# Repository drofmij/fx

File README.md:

# FX 
This repo will hold any schematic / pcb board combinations in Eagle cad format that I am working on. They may or may not work or be useful to anyone. Most of what I have been working on are in the form of boards for guitar effects.

## Projects
- [Attack of the Klones](https://github.com/drofmij/fx/tree/master/klones) (Unverified)
- [Mandarin AD200B](https://github.com/drofmij/fx/tree/master/Baja-Orange-AD200B) (Unverified)

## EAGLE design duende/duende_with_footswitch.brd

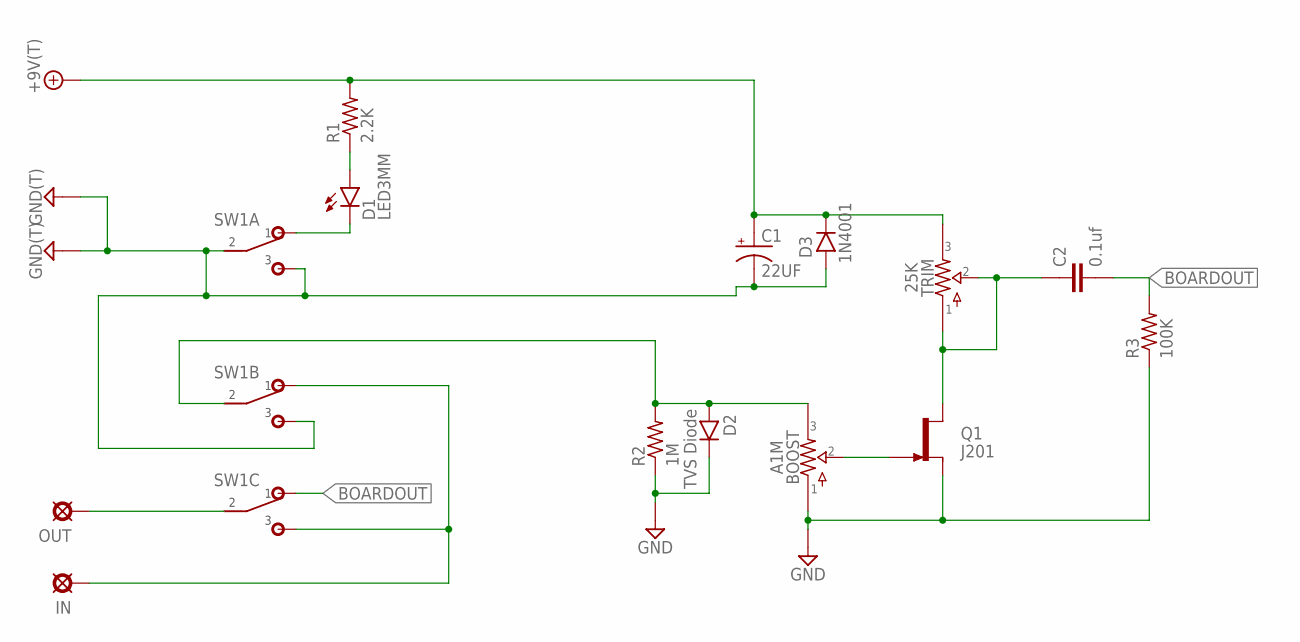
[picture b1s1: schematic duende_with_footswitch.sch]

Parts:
+9V: +9V(T); SQUARE
BOOST: A1M; PADS_SMALL
C1: 22UF; 050_020_1
C2: 0.1uf; 072X025
D1: LED3MM
D2: TVS Diode; DO41-2
D3: 1N4001; DO41-2
GND, GND1: GND(T); SQUARE
IN: PADO; ROUND
OUT: PADO; ROUND
Q1: J201; TO92-
R1: 2.2K; R0207/3
R2: 1M; R0207/3
R3: 100K; R0207/3
SW1: 3PDT
TRIM: 25K; TRIM-ALL

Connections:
+9V: +9V.1, C1.+, D3.C, R1.2, TRIM.3, TRIM.6 (3)
BOARDIN: BOOST.3, D2.A, R2.2, SW1.B2 (2)
BOARDOUT: C2.2, R3.2, SW1.C1 (1)
GND: BOOST.1, C1.-, D2.C, D3.A, GND.1, GND1.1, Q1.2 (S), R2.1, R3.1, SW1.A2 (2), SW1.A3 (3), SW1.B3 (3)
INPUT: IN.1, SW1.B1 (1), SW1.C3 (3)
unnamed: D1.K (C), SW1.A1 (1)
unnamed: D1.A, R1.1
unnamed: BOOST.2, Q1.1 (G)
unnamed: C2.1, Q1.3 (D), TRIM.1, TRIM.2, TRIM.4 (1), TRIM.5 (2)
OUTPUT: OUT.1, SW1.C2 (2)

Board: 2 copper layers, 17 parts (0 on the bottom side), 10 nets, no tracks yet.

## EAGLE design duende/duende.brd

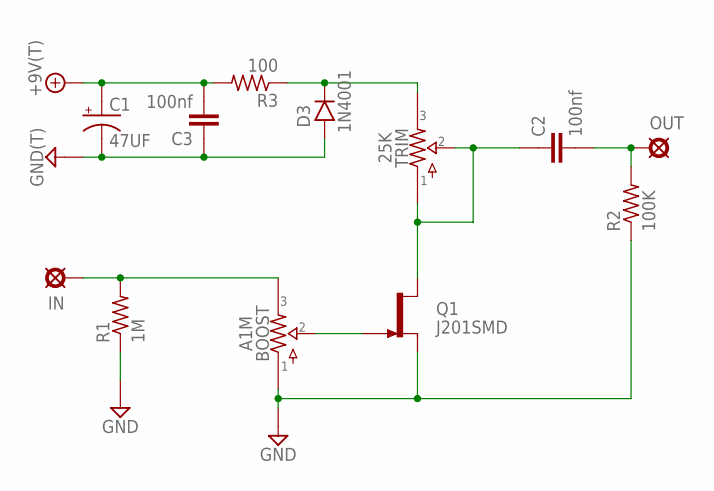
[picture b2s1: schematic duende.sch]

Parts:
+9V: +9V(T); SQUARE
BOOST: A1M; PADS_SMALL
C1: 47UF; 050_020_1
C2, C3: 100nf; 072X025
D3: 1N4001; DO41-2
GND: GND(T); SQUARE
IN: IN]; ROUND
OUT: OUT; ROUND
Q1: J201SMD; SOT23
R1: 1M; R0204/2
R2: 100K; R0204/2
R3: 100; R0204/2
TRIM: 25K; TRIM-ALL

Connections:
+9V: +9V.1, C1.+, C3.2, R3.2
FXOUT: C2.2, OUT.1, R2.2
GND: BOOST.1, C1.-, C3.1, D3.A, GND.1, Q1.E (S), R1.1, R2.1
unnamed: BOOST.3, IN.1, R1.2
unnamed: D3.C, R3.1, TRIM.3, TRIM.6 (3)
unnamed: BOOST.2, Q1.C (G)
unnamed: C2.1, Q1.B (D), TRIM.1, TRIM.2, TRIM.4 (1), TRIM.5 (2)

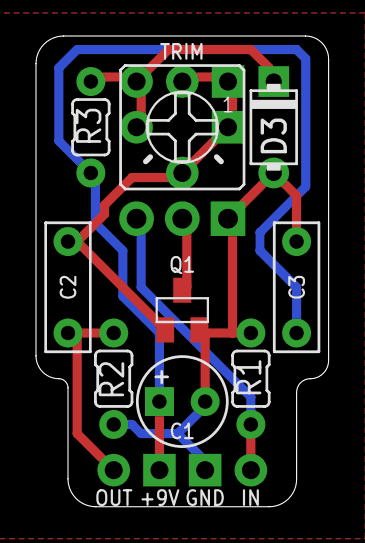
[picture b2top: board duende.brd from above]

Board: 2 copper layers, 16.3 x 26.2 mm, 14 parts (1 on the bottom side), 7 nets.

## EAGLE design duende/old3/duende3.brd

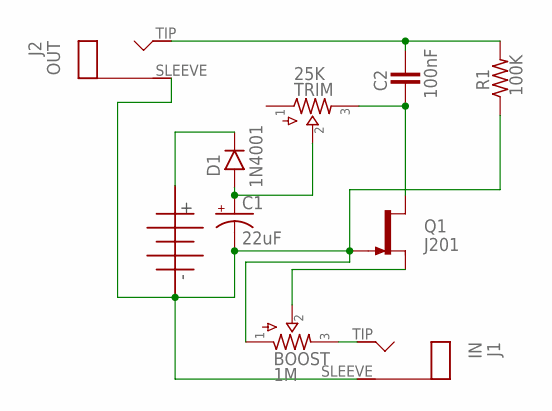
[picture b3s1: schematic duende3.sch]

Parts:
+9V: +9V; BATTERY
BOOST: 1M; PADS_LARGE
C1: 22uF; 050_020_1
C2: 100nF; BOX_SMALL
D1: 1N4001; DO41-3
J1: IN; TWO_PADS
J2: OUT; TWO_PADS
Q1: J201; TO92-
R1: 100K; R0207/3
TRIM: 25K; 2262_TRIM

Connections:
GND: +9V.P$2, BOOST.1, C1.-, J1.SLEEVE, J2.SLEEVE, Q1.1 (G), R1.1
unnamed: +9V.P$1, D1.C
unnamed: C1.+, D1.A, TRIM.2
unnamed: BOOST.2, Q1.2 (S)
unnamed: C2.2, Q1.3 (D), TRIM.3
unnamed: C2.1, J2.TIP, R1.2
unnamed: BOOST.3, J1.TIP

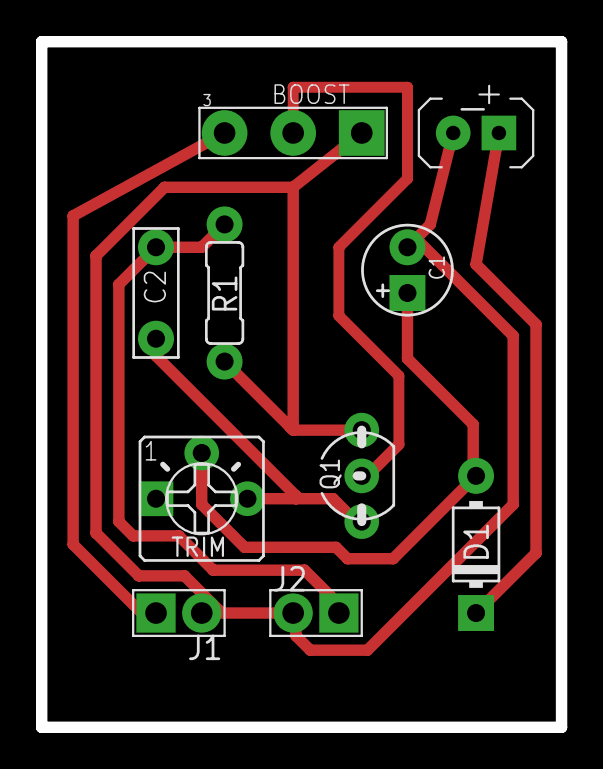
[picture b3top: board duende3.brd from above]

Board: 2 copper layers, 28.9 x 38.1 mm, 10 parts (0 on the bottom side), 7 nets.

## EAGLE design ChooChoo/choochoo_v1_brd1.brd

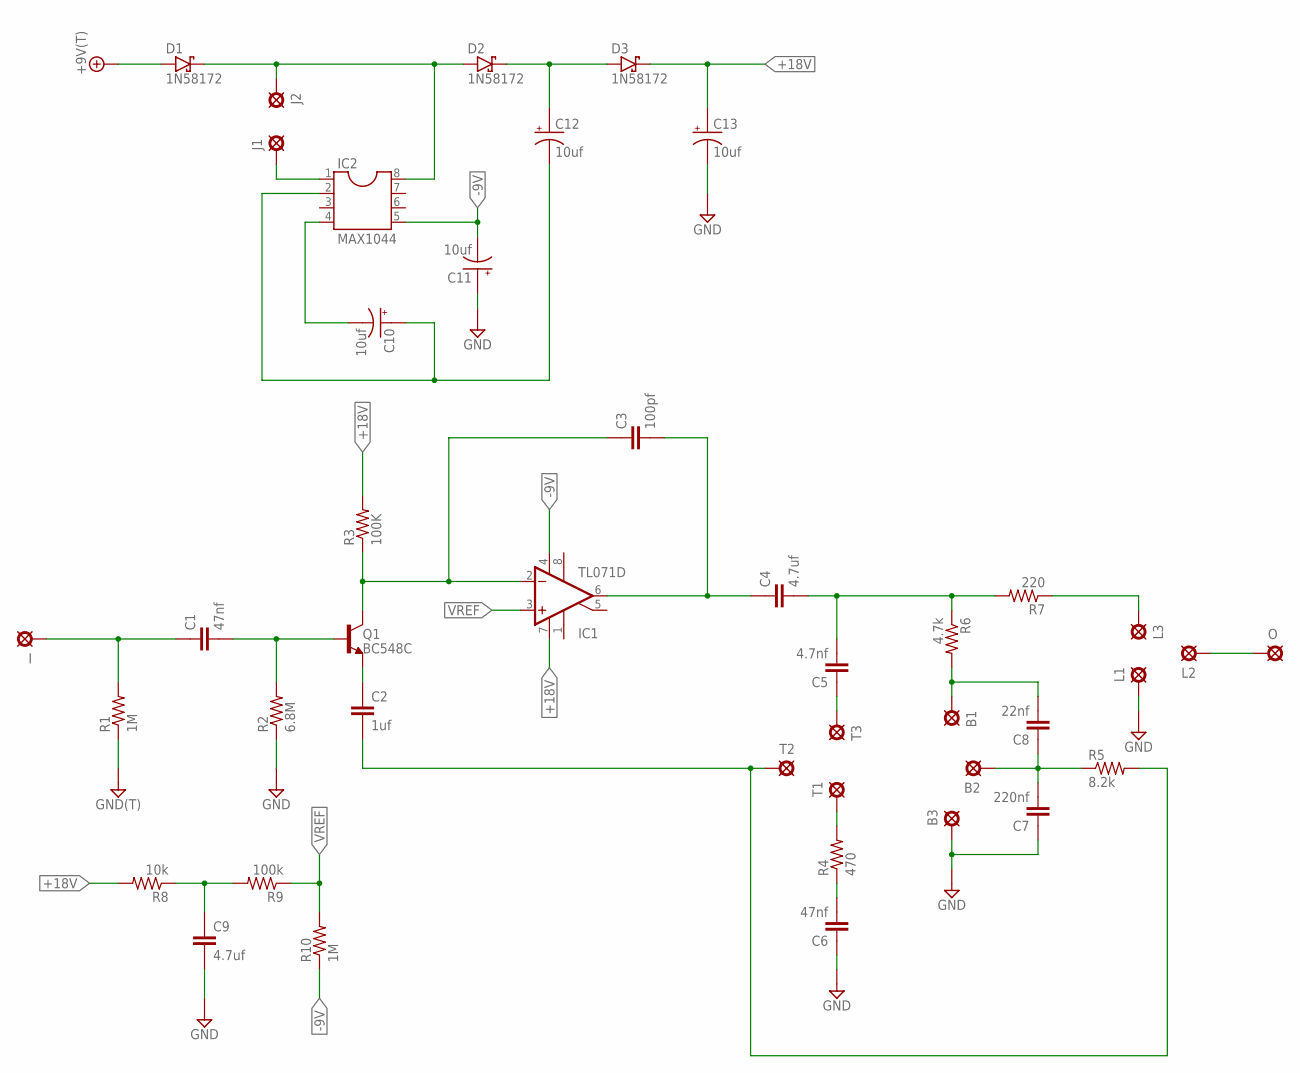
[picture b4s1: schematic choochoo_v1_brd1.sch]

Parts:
B1, B2, B3: PAD8; OCTOGON
C1, C6: 47nf; 072X025
C2: 1uf; 050X030_025
C3: 100pf; 050X030_025
C4, C9: 4.7uf; 050X030_025
C5: 4.7nf; 072X025
C7: 220nf; 072X025
C8: 22nf; 072X025
C10, C11, C12, C13: 10uf; 050_020_1
D1, D2, D3: 1N58172; DO41-2
G: GND(T); SQUARE
I: IN; ROUND
IC1: TL071D; SO08
IC2: MAX1044; DIL08
J1, J2: PAD8; OCTOGON
L1, L2, L3: PAD8; OCTOGON
O: IN; ROUND
Q1: BC548C; TO92-
R1, R10: 1M; R0204/2
R2: 6.8M; R0204/2
R3: 100K; R0204/2
R4: 470; R0204/2
R5: 8.2k; R0204/2
R6: 4.7k; R0204/2
R7: 220; R0204/2
R8: 10k; R0204/2
R9: 100k; R0204/2
T1, T2, T3: PAD8; OCTOGON
V: +9V(T); SQUARE

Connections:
+9V: D1.A, V.1
+18V: C13.+, D3.C, IC1.7 (V+), R3.2, R8.2
-9V: C11.-, IC1.4 (V-), IC2.5, R10.1
GND: B3.1, C6.1, C7.1, C9.2, C11.+, C13.-, G.1, L1.1, R1.1, R2.1
unnamed: D1.C, D2.A, IC2.8, J2.1
unnamed: C1.2, Q1.1 (B), R2.2
unnamed: C3.1, IC1.2 (-IN), Q1.2 (C), R3.1
unnamed: C2.1, Q1.3 (E)
unnamed: R4.2, T1.1
unnamed: C3.2, C4.1, IC1.6 (OUT)
unnamed: C5.1, T3.1
unnamed: C4.2, C5.2, R6.1, R7.2
unnamed: L3.1, R7.1
unnamed: C6.2, R4.1
unnamed: C12.+, D2.C, D3.A
unnamed: L2.1, O.1
unnamed: B1.1, C8.2, R6.2
unnamed: B2.1, C7.2, C8.1, R5.1
unnamed: C9.1, R8.1, R9.2
unnamed: C2.2, R5.2, T2.1
unnamed: C10.+, C12.-, IC2.2
unnamed: C10.-, IC2.4
unnamed: IC2.1, J1.1
unnamed: C1.1, I.1, R1.2
VREF: IC1.3 (+IN), R9.1, R10.2

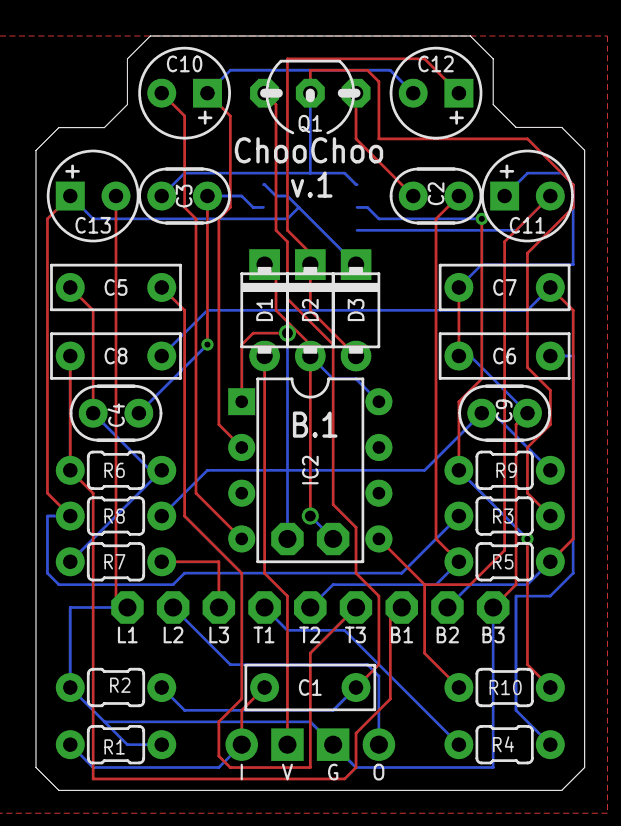
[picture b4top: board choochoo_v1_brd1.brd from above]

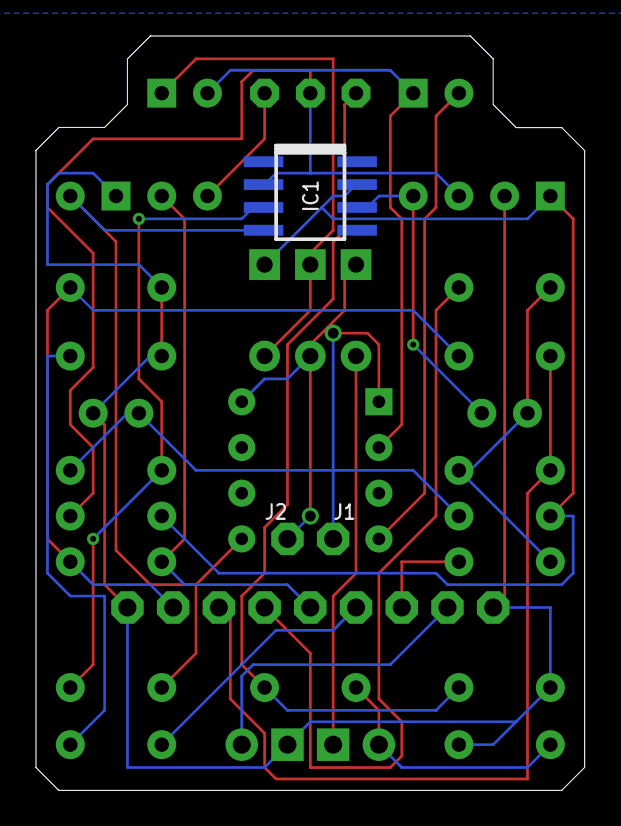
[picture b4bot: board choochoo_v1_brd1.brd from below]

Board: 2 copper layers, 30.5 x 41.9 mm, 44 parts (3 on the bottom side), 25 nets.

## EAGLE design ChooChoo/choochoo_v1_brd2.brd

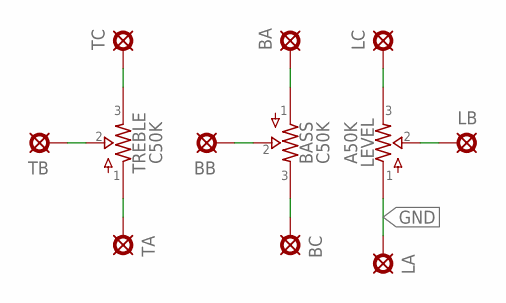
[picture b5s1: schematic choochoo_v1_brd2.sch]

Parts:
BA: PAD8; OCTOGON
BASS: C50K; 9MM_W/MOUNTS-2MMHOLES
BB: PAD8; OCTOGON
BC: PAD8; OCTOGON
LA: PAD8; OCTOGON
LB: PAD8; OCTOGON
LC: PAD8; OCTOGON
LEVEL: A50K; 9MM_W/MOUNTS-2MMHOLES
TA: PAD8; OCTOGON
TB: PAD8; OCTOGON
TC: PAD8; OCTOGON
TREBLE: C50K; 9MM_W/MOUNTS-2MMHOLES

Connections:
GND: LA.1, LEVEL.P$1 (1)
unnamed: TB.1, TREBLE.P$2 (2)
unnamed: TC.1, TREBLE.P$3 (3)
unnamed: TA.1, TREBLE.P$1 (1)
unnamed: BASS.P$3 (3), BC.1
unnamed: BASS.P$2 (2), BB.1
unnamed: BA.1, BASS.P$1 (1)
unnamed: LB.1, LEVEL.P$2 (2)
unnamed: LC.1, LEVEL.P$3 (3)

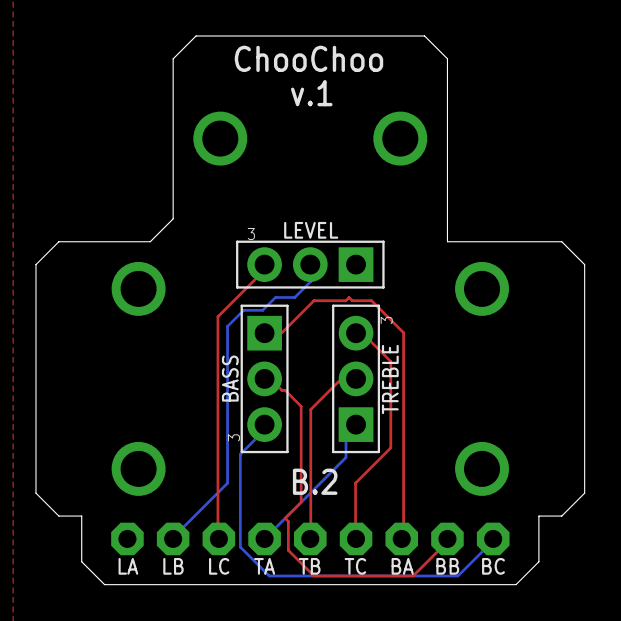
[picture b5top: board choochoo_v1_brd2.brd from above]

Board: 2 copper layers, 30.5 x 30.5 mm, 12 parts (0 on the bottom side), 9 nets.

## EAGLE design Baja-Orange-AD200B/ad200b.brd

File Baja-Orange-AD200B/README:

This is based on Baja's Clone of the Orange AD200B preamp. I built this per Johnk's version on the [original thread](http://freestompboxes.org/viewtopic.php?f=13&t=28961&view=unread&sid=48e1a8c39ae74f20a4534faedff610bc)

My understanding is that Baja built this preamp using the frequency and clipping characteristics of the original amp, as such it is not a part for part copy of the original.

Currently UNVERIFIED and planning to fit it into a 1590b once I have time to order boards and build it. If you build this before I get to it please let me know how it works out.

Transistor and opamp are SMD / SMT but should not be too bad. for the 1uf caps I was planning on using tantalum or mlcc so used a footprint that will allow it instead of the normal electrolytic ones. The board allows for top mount IN OUT jacks and top mount power jack if you want to use them.

PLEASE NOTE: I designed this to be used in conjunction with a 3pdt daughter board which has power filtering on it. As such I did not add proper power filtering to this schem / board

- [Eagle cad files](https://github.com/drofmij/fx/tree/master/Baja-Orange-AD200B)
- [Parts list CSV](https://raw.githubusercontent.com/drofmij/fx/master/Baja-Orange-AD200B/ad200b-bom.csv)

Final NOTE / Warning: This is entirely untested, I am open to input but will likely respond very asynchronously as Real Life is a bit crazy right now. There is no warranty or support included with this design.

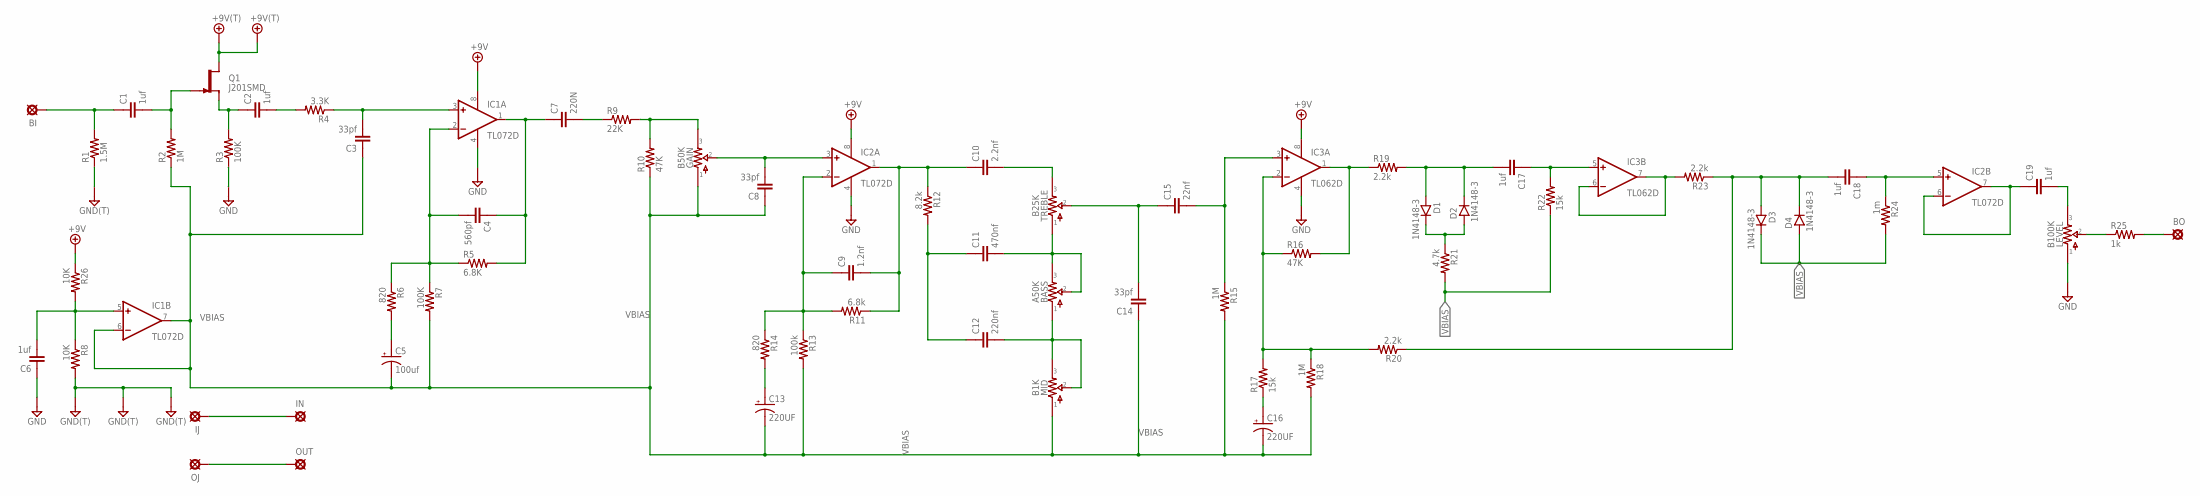
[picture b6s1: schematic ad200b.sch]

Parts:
+V: +9V(T); SQUARE
BASS: A50K; 9MM_W/MOUNTS-2MMHOLES
BI: IN; SQUARE
BO: OUT; SQUARE
C1, C2, C6, C17, C18, C19: 1uf; 050X030_025
C3, C8, C14: 33pf; 050X030_025
C4: 560pf; 050X030_025
C5: 100uf; 050_020_1
C7: 220N; 072X025
C9: 1.2nf; 072X025
C10: 2.2nf; 072X025
C11: 470nf; 072X025
C12: 220nf; 072X025
C13, C16: 220UF; 050_020_1
C15: 22nf; 072X025
D1, D2, D3, D4: 1N4148-3; DO35-3
G1, G2, G3, G4: GND(T); SQUARE
GAIN: B50K; 9MM_W/MOUNTS-2MMHOLES
IC1, IC2: TL072D; SO08
IC3: TL062D; SO08
IJ: PAD8; OCTOGON
IN: PAD8; OCTOGON
LEVEL: B100K; 9MM_W/MOUNTS-2MMHOLES
MID: B1K; 9MM_W/MOUNTS-2MMHOLES
OJ: PAD8; OCTOGON
OUT: PAD8; OCTOGON
Q1: J201SMD; SOT23
R1: 1.5M; R0204/2
R2, R15, R18: 1M; R0204/2
R3, R7: 100K; R0204/2
R4: 3.3K; R0204/2
R5: 6.8K; R0204/2
R6, R14: 820; R0204/2
R8, R26: 10K; R0204/2
R9: 22K; R0204/2
R10, R16: 47K; R0204/2
R11: 6.8k; R0204/2
R12: 8.2k; R0204/2
R13: 100k; R0204/2
R17, R22: 15k; R0204/2
R19, R20, R23: 2.2k; R0204/2
R21: 4.7k; R0204/2
R24: 1m; R0204/2
R25: 1k; R0204/2
TREBLE: B25K; 9MM_W/MOUNTS-2MMHOLES
V: +9V(T); SQUARE

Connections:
+9V: +V.1, IC1.8 (V+), IC2.8 (V+), IC3.8 (V+), Q1.B (D), R26.1, V.1
GND: C6.1, G1.1, G2.1, G3.1, G4.1, IC1.4 (V-), IC2.4 (V-), IC3.4 (V-), LEVEL.P$1 (1), R1.1, R3.1, R8.2
unnamed: BI.1, C1.1, R1.2
unnamed: C1.2, Q1.C (G), R2.2
unnamed: C2.1, Q1.E (S), R3.2
unnamed: C2.2, R4.2
unnamed: C6.2, IC1.5 (+IN), R8.1, R26.2
unnamed: C3.2, IC1.3 (+IN), R4.1
unnamed: C4.2, IC1.2 (-IN), R5.1, R6.1, R7.1
unnamed: C4.1, C7.1, IC1.1 (OUT), R5.2
unnamed: C7.2, R9.1
unnamed: GAIN.P$3 (3), R9.2, R10.2
unnamed: C5.+, R6.2
unnamed: C9.2, C10.1, IC2.1 (OUT), R11.1, R12.1
unnamed: BASS.P$1 (1), C12.2, MID.P$2 (2), MID.P$3 (3)
unnamed: C11.1, C12.1, R12.2
unnamed: C8.2, GAIN.P$2 (2), IC2.3 (+IN)
unnamed: IC3.1 (OUT), R16.2, R19.1
unnamed: C17.1, IC3.5 (+IN), R22.2
unnamed: C9.1, IC2.2 (-IN), R11.2, R13.1, R14.1
unnamed: BASS.P$2 (2), BASS.P$3 (3), C11.2, TREBLE.P$1 (1)
unnamed: C13.+, R14.2
unnamed: C17.2, D1.A, D2.C, R19.2
unnamed: C10.2, TREBLE.P$3 (3)
unnamed: D1.C, D2.A, R21.1
unnamed: C14.2, C15.1, TREBLE.P$2 (2)
unnamed: IC3.6 (-IN), IC3.7 (OUT), R23.2
unnamed: C15.2, IC3.3 (+IN), R15.1
unnamed: C18.2, D3.A, D4.C, R20.1, R23.1
unnamed: C19.1, IC2.6 (-IN), IC2.7 (OUT)
unnamed: C16.+, R17.1
unnamed: IJ.1, IN.1
unnamed: C19.2, LEVEL.P$3 (3)
unnamed: IC3.2 (-IN), R16.1, R17.2, R18.1, R20.2
unnamed: C18.1, IC2.5 (+IN), R24.1
unnamed: OJ.1, OUT.1
unnamed: LEVEL.P$2 (2), R25.1
unnamed: BO.1, R25.2
VBIAS: C3.1, C5.-, C8.1, C13.-, C14.1, C16.-, D3.C, D4.A, GAIN.P$1 (1), IC1.6 (-IN), IC1.7 (OUT), MID.P$1 (1), R2.1, R7.2, R10.1, R13.2, R15.2, R18.2, R21.2, R22.1, R24.2

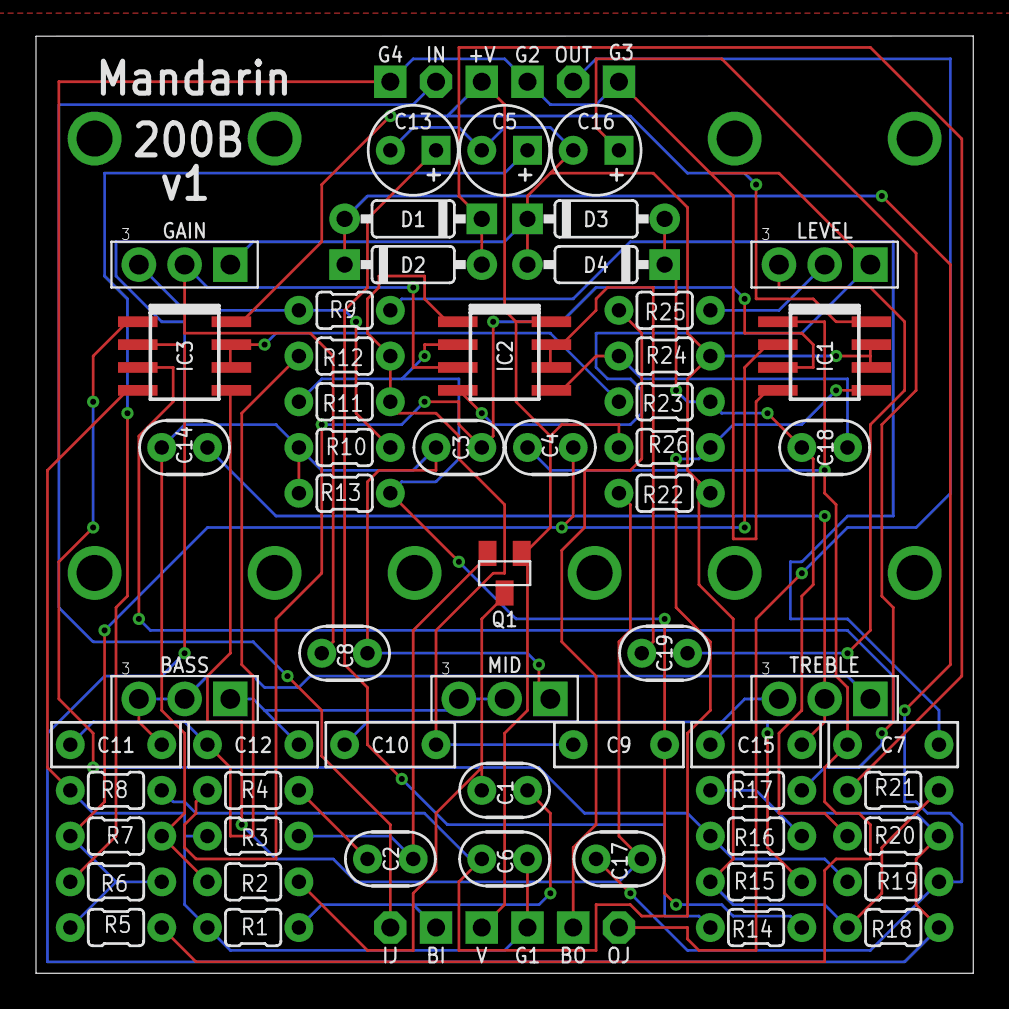
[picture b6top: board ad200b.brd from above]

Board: 2 copper layers, 52.1 x 52.1 mm, 70 parts (0 on the bottom side), 39 nets.

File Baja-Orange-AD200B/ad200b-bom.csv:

"Part";"Value";"Device";"Package";"Description";"";
"+V";"+9V(T)";"+9V(T)";"SQUARE";"+9V Voltage Supply";"";
"BASS";"A50K";"POTS9MM_MOUNTED_2MMH";"9MM_W/MOUNTS-2MMHOLES";"";"";
"BI";"IN";"PAD";"SQUARE";"PAD";"";
"BO";"OUT";"PAD";"SQUARE";"PAD";"";
"C1";"1uf";"050X030_0251";"050X030_025";"47 - 120pF";"";
"C2";"1uf";"050X030_0251";"050X030_025";"47 - 120pF";"";
"C3";"33pf";"050X030_0251";"050X030_025";"47 - 120pF";"";
"C4";"560pf";"050X030_0251";"050X030_025";"47 - 120pF";"";
"C5";"100uf";"0501";"050_020_1";"0.22 - 100uF";"";
"C6";"1uf";"050X030_0251";"050X030_025";"47 - 120pF";"";
"C7";"220N";"072X0252";"072X025";"1000pF - 0.47uF";"";
"C8";"33pf";"050X030_0251";"050X030_025";"47 - 120pF";"";
"C9";"1.2nf";"072X0252";"072X025";"1000pF - 0.47uF";"";
"C10";"2.2nf";"072X0252";"072X025";"1000pF - 0.47uF";"";
"C11";"470nf";"072X0252";"072X025";"1000pF - 0.47uF";"";
"C12";"220nf";"072X0252";"072X025";"1000pF - 0.47uF";"";
"C13";"220UF";"0501";"050_020_1";"0.22 - 100uF";"";
"C14";"33pf";"050X030_0251";"050X030_025";"47 - 120pF";"";
"C15";"22nf";"072X0252";"072X025";"1000pF - 0.47uF";"";
"C16";"220UF";"0501";"050_020_1";"0.22 - 100uF";"";
"C17";"1uf";"050X030_0251";"050X030_025";"47 - 120pF";"";
"C18";"1uf";"050X030_0251";"050X030_025";"47 - 120pF";"";
"C19";"1uf";"050X030_0251";"050X030_025";"47 - 120pF";"";
"D1";"1N4148-3";"1N4148-3";"DO35-3";"Fast Switching Diode";"";
"D2";"1N4148-3";"1N4148-3";"DO35-3";"Fast Switching Diode";"";
"D3";"1N4148-3";"1N4148-3";"DO35-3";"Fast Switching Diode";"";
"D4";"1N4148-3";"1N4148-3";"DO35-3";"Fast Switching Diode";"";
"G1";"GND(T)";"GND(T)";"SQUARE";"Ground";"";
"G2";"GND(T)";"GND(T)";"SQUARE";"Ground";"";
"G3";"GND(T)";"GND(T)";"SQUARE";"Ground";"";
"G4";"GND(T)";"GND(T)";"SQUARE";"Ground";"";
"GAIN";"B50K";"POTS9MM_MOUNTED_2MMH";"9MM_W/MOUNTS-2MMHOLES";"";"";
"IC1";"TL072D";"TL072D";"SO08";"OP AMP";"";
"IC2";"TL072D";"TL072D";"SO08";"OP AMP";"";
"IC3";"TL062D";"TL062D";"SO08";"OP AMP";"";
"IJ";"";"PAD8";"OCTOGON";"PAD";"";
"IN";"";"PAD8";"OCTOGON";"PAD";"";
"LEVEL";"B100K";"POTS9MM_MOUNTED_2MMH";"9MM_W/MOUNTS-2MMHOLES";"";"";
"MID";"B1K";"POTS9MM_MOUNTED_2MMH";"9MM_W/MOUNTS-2MMHOLES";"";"";
"OJ";"";"PAD8";"OCTOGON";"PAD";"";
"OUT";"";"PAD8";"OCTOGON";"PAD";"";
"Q1";"J201SMD";"J201SMD";"SOT23";"N-channel JFET";"";
"R1";"1.5M";"3MM.2";"R0204/2";"3mm Resistors";"";
"R2";"1M";"3MM.2";"R0204/2";"3mm Resistors";"";
"R3";"100K";"3MM.2";"R0204/2";"3mm Resistors";"";
"R4";"3.3K";"3MM.2";"R0204/2";"3mm Resistors";"";
"R5";"6.8K";"3MM.2";"R0204/2";"3mm Resistors";"";
"R6";"820";"3MM.2";"R0204/2";"3mm Resistors";"";
"R7";"100K";"3MM.2";"R0204/2";"3mm Resistors";"";
"R8";"10K";"3MM.2";"R0204/2";"3mm Resistors";"";
"R9";"22K";"3MM.2";"R0204/2";"3mm Resistors";"";
"R10";"47K";"3MM.2";"R0204/2";"3mm Resistors";"";
"R11";"6.8k";"3MM.2";"R0204/2";"3mm Resistors";"";
"R12";"8.2k";"3MM.2";"R0204/2";"3mm Resistors";"";
"R13";"100k";"3MM.2";"R0204/2";"3mm Resistors";"";
"R14";"820";"3MM.2";"R0204/2";"3mm Resistors";"";
"R15";"1M";"3MM.2";"R0204/2";"3mm Resistors";"";
"R16";"47K";"3MM.2";"R0204/2";"3mm Resistors";"";
"R17";"15k";"3MM.2";"R0204/2";"3mm Resistors";"";
"R18";"1M";"3MM.2";"R0204/2";"3mm Resistors";"";
"R19";"2.2k";"3MM.2";"R0204/2";"3mm Resistors";"";
"R20";"2.2k";"3MM.2";"R0204/2";"3mm Resistors";"";
"R21";"4.7k";"3MM.2";"R0204/2";"3mm Resistors";"";
"R22";"15k";"3MM.2";"R0204/2";"3mm Resistors";"";
"R23";"2.2k";"3MM.2";"R0204/2";"3mm Resistors";"";
"R24";"1m";"3MM.2";"R0204/2";"3mm Resistors";"";
"R25";"1k";"3MM.2";"R0204/2";"3mm Resistors";"";
"R26";"10K";"3MM.2";"R0204/2";"3mm Resistors";"";
"TREBLE";"B25K";"POTS9MM_MOUNTED_2MMH";"9MM_W/MOUNTS-2MMHOLES";"";"";
"V";"+9V(T)";"+9V(T)";"SQUARE";"+9V Voltage Supply";"";

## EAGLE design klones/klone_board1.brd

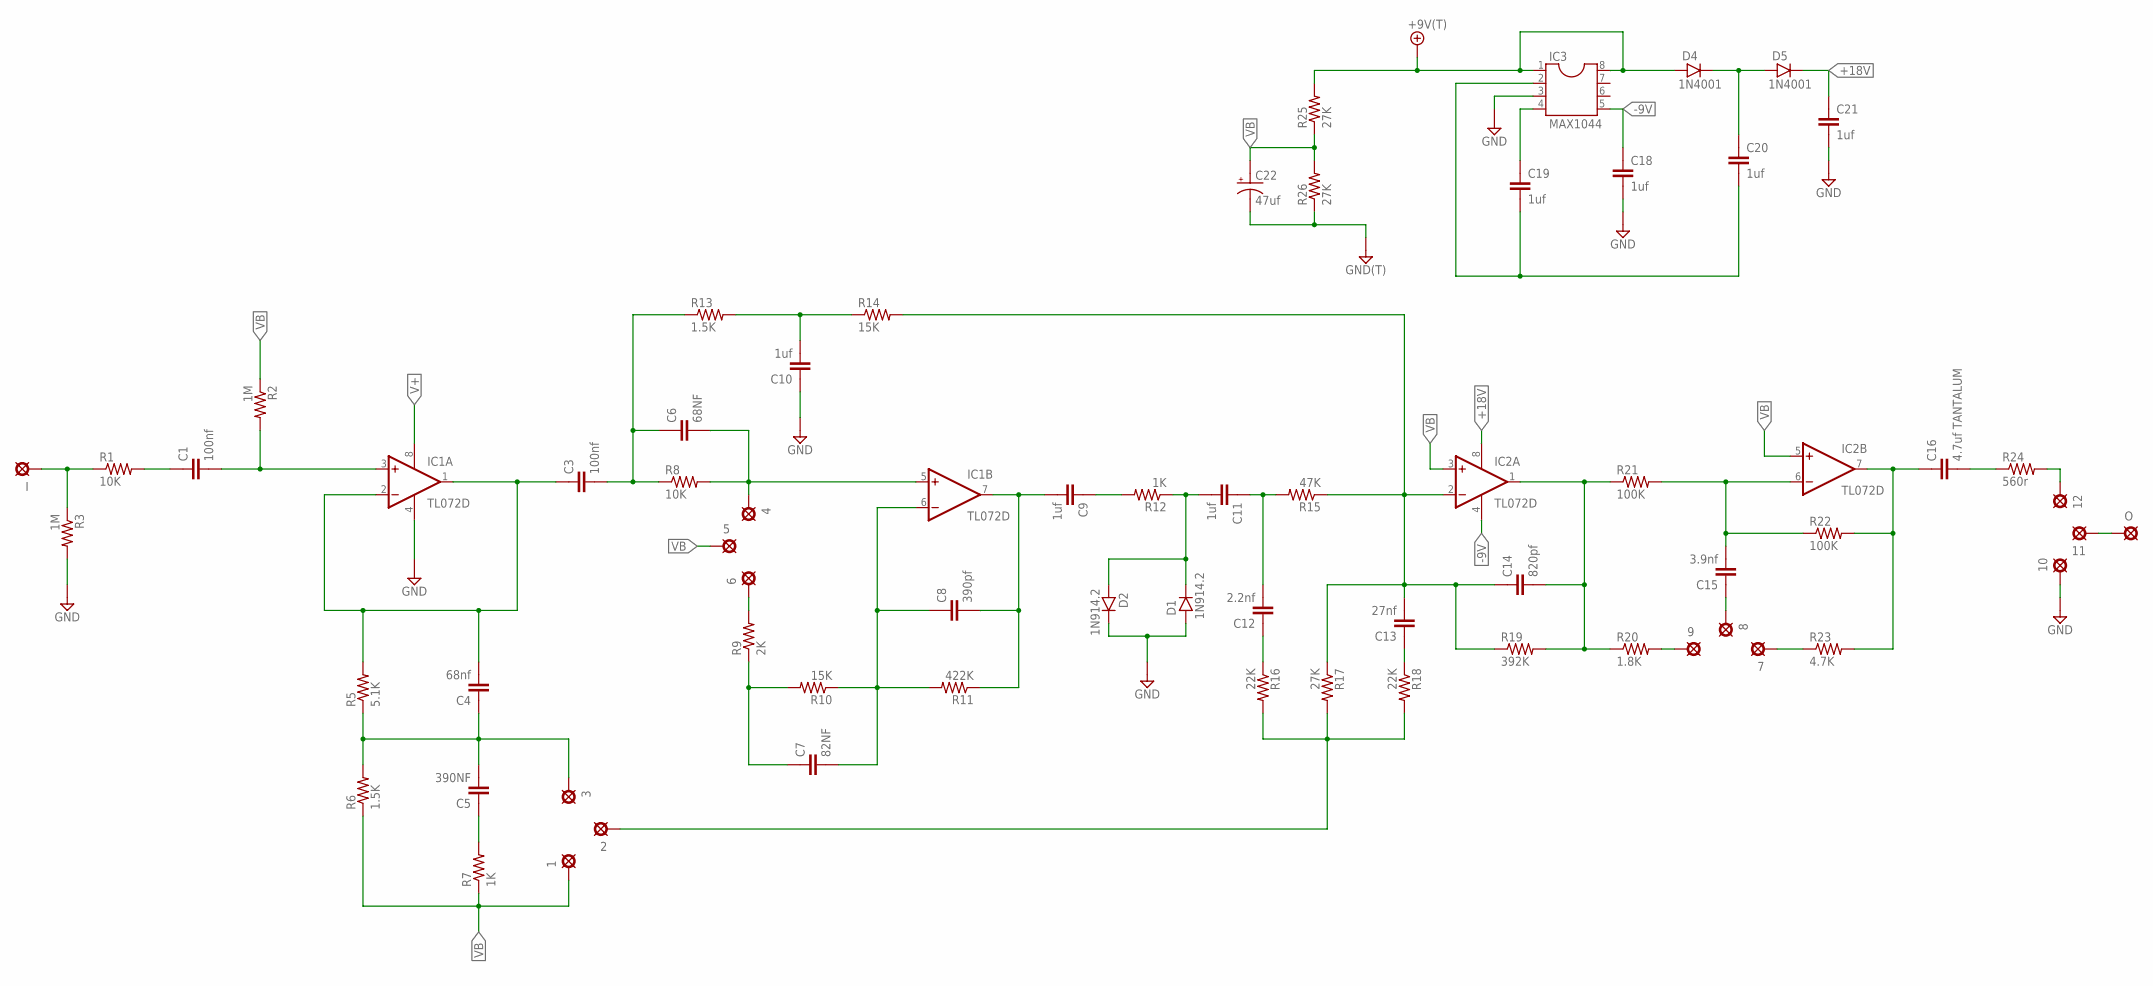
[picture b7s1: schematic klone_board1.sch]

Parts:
1, 2, 3, 4, 5, 6, 7, 8, 9, 10, 11, 12: PAD; SQUARE
C1, C3: 100nf; 072X025
C4: 68nf; 072X025
C5: 390NF; 072X025
C6: 68NF; 072X025
C7: 82NF; 072X025
C8: 390pf; 050X030_025
C9, C10, C11, C18, C19, C20, C21: 1uf; 050X030_025
C12: 2.2nf; 072X025
C13: 27nf; 072X025
C14: 820pf; 050X030_025
C15: 3.9nf; 072X025
C16: 4.7uf TANTALUM; 050X030_025
C22: 47uf; 050_020_1
D1, D2: 1N914.2; DO35-2
D4, D5: 1N4001; DO41-2
G: GND(T); SQUARE
I: IN; SQUARE
IC1, IC2: TL072D; SO08
IC3: MAX1044; SO08
O: OUT; SQUARE
R1, R8: 10K; R0204/2
R2, R3: 1M; R0204/2
R5: 5.1K; R0204/2
R6, R13: 1.5K; R0204/2
R7, R12: 1K; R0204/2
R9: 2K; R0204/2
R10, R14: 15K; R0204/2
R11: 422K; R0204/2
R15: 47K; R0204/2
R16, R18: 22K; R0204/2
R17, R25, R26: 27K; R0204/2
R19: 392K; R0204/2
R20: 1.8K; R0204/2
R21, R22: 100K; R0204/2
R23: 4.7K; R0204/2
R24: 560r; R0204/2
V: +9V(T); SQUARE

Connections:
+18V: C21.1, D5.C, IC2.8 (V+)
-9V: C18.1, IC2.4 (V-), IC3.5
GND: 10.1, C10.1, C18.2, C21.2, C22.-, D1.A, D2.C, G.1, IC1.4 (V-), IC3.3, R3.2, R26.1
unnamed: I.1, R1.1, R3.1
unnamed: C1.1, R1.2
unnamed: C1.2, IC1.3 (+IN), R2.2
unnamed: C3.1, C4.2, IC1.1 (OUT), IC1.2 (-IN), R5.2
unnamed: C3.2, C6.1, R8.1, R13.1
unnamed: 4.1, C6.2, IC1.5 (+IN), R8.2
unnamed: 6.1, R9.2
unnamed: C7.1, R9.1, R10.2
unnamed: C7.2, C8.1, IC1.6 (-IN), R10.1, R11.2
unnamed: C8.2, C9.2, IC1.7 (OUT), R11.1
unnamed: C10.2, R13.2, R14.1
unnamed: 3.1, C4.1, C5.2, R5.1, R6.2
unnamed: C11.1, C12.2, R15.2
unnamed: C11.2, D1.C, D2.A, R12.1
unnamed: C9.1, R12.2
unnamed: C5.1, R7.2
unnamed: C12.1, R16.1
unnamed: 9.1, R20.2
unnamed: 2.1, R16.2, R17.2, R18.2
unnamed: 7.1, R23.1
unnamed: C13.1, R18.1
unnamed: C14.2, IC2.1 (OUT), R19.2, R20.1, R21.1
unnamed: C13.2, C14.1, IC2.2 (-IN), R14.2, R15.1, R17.1, R19.1
unnamed: C15.2, IC2.6 (-IN), R21.2, R22.1
unnamed: 8.1, C15.1
unnamed: C16.1, IC2.7 (OUT), R22.2, R23.2
unnamed: C16.2, R24.1
unnamed: 12.1, R24.2
unnamed: 11.1, O.1
unnamed: C20.1, D4.C, D5.A
unnamed: C19.2, C20.2, IC3.2
unnamed: C19.1, IC3.4
V+: D4.A, IC1.8 (V+), IC3.1, IC3.8, R25.2, V.1
VB: 1.1, 5.1, C22.+, IC2.3 (+IN), IC2.5 (+IN), R2.1, R6.1, R7.1, R25.1, R26.2

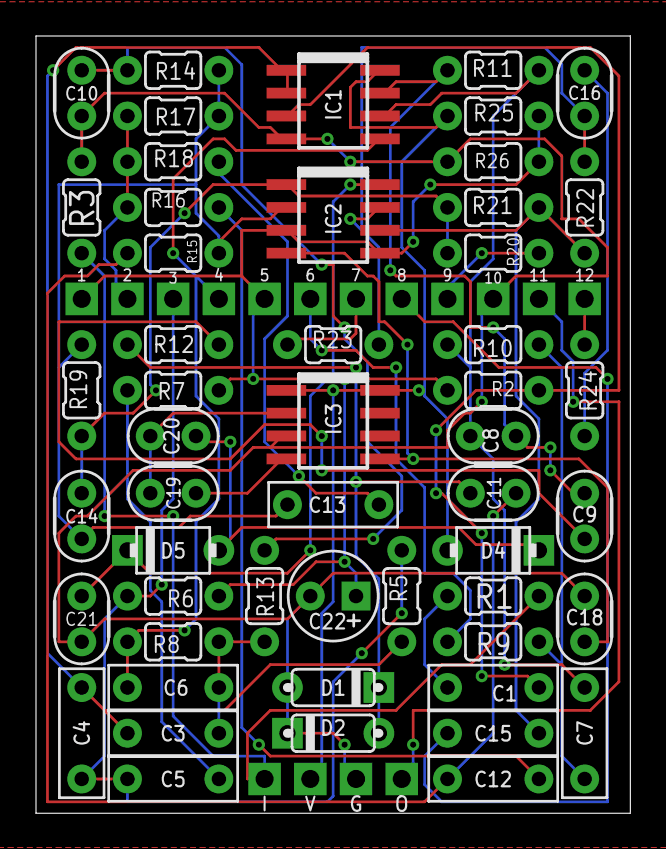
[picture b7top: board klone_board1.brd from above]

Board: 2 copper layers, 33.0 x 43.2 mm, 68 parts (0 on the bottom side), 37 nets.

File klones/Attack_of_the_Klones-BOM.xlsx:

Part | Value | Device | Package | Library | Sheet
GAIN | 9MM_DUALGANG | kdd-mb-pots | (575 | 675) | MR0
TONE | 9MM_W/MOUNTS-2MMHOLES | kdd-mb-pots | (475 | 400) | R90
VOL | 9MM_W/MOUNTS-2MMHOLES | kdd-mb-pots | (675 | 400) | R270
C1 | 100nf | 072X0252 | 072X025 | kdd-caps-film-box | 1
C3 | 100nf | 072X0252 | 072X025 | kdd-caps-film-box | 1
C4 | 68nf | 072X0252 | 072X025 | kdd-caps-film-box | 1
C5 | 390NF | 072X0252 | 072X025 | kdd-caps-film-box | 1
C6 | 68NF | 072X0252 | 072X025 | kdd-caps-film-box | 1
C7 | 82NF | 072X0252 | 072X025 | kdd-caps-film-box | 1
C8 | 390pf | 050X030_0251 | 050X030_025 | kdd-caps-ceramic | 1
C9 | 1uf | 050X030_0251 | 050X030_025 | kdd-caps-ceramic | 1
C10 | 1uf | 050X030_0251 | 050X030_025 | kdd-caps-ceramic | 1
C11 | 1uf | 050X030_0251 | 050X030_025 | kdd-caps-ceramic | 1
C12 | 2.2nf | 072X0252 | 072X025 | kdd-caps-film-box | 1
C13 | 27nf | 072X0252 | 072X025 | kdd-caps-film-box | 1
C14 | 820pf | 050X030_0251 | 050X030_025 | kdd-caps-ceramic | 1
C15 | 3.9nf | 072X0252 | 072X025 | kdd-caps-film-box | 1
C16 | 4.7uf | TANTALUM | 050X030_0251 | 050X030_025 | 1
C18 | 1uf | 050X030_0251 | 050X030_025 | kdd-caps-ceramic | 1
C19 | 1uf | 050X030_0251 | 050X030_025 | kdd-caps-ceramic | 1
C20 | 1uf | 050X030_0251 | 050X030_025 | kdd-caps-ceramic | 1
C21 | 1uf | 050X030_0251 | 050X030_025 | kdd-caps-ceramic | 1
C22 | 47uf | 501 | 050_020_1 | kdd-caps-electro-pol | 1
D1 | 1N914.2 | 1N914.2 | DO35-2 | kdd-diodes | 1
D2 | 1N914.2 | 1N914.2 | DO35-2 | kdd-diodes | 1
D4 | 1N4001 | 1N400X.2 | DO41-2 | kdd-diodes | 1
D5 | 1N4001 | 1N400X.2 | DO41-2 | kdd-diodes | 1
IC1 | TL072D | TL072D | SO08 | kdd-ics | 1
IC2 | TL072D | TL072D | SO08 | kdd-ics | 1
IC3 | MAX1044 | DIL8SMD | SO08 | kdd-ics | 1
R1 | 10K | 3MM.2 | R0204/2 | kdd-resistors | 1
R2 | 1M | 3MM.2 | R0204/2 | kdd-resistors | 1
R3 | 1M | 3MM.2 | R0204/2 | kdd-resistors | 1
R5 | 5.1K | 3MM.2 | R0204/2 | kdd-resistors | 1
R6 | 1.5K | 3MM.2 | R0204/2 | kdd-resistors | 1
R7 | 1K | 3MM.2 | R0204/2 | kdd-resistors | 1
R8 | 10K | 3MM.2 | R0204/2 | kdd-resistors | 1
R9 | 2K | 3MM.2 | R0204/2 | kdd-resistors | 1
R10 | 15K | 3MM.2 | R0204/2 | kdd-resistors | 1
R11 | 422K | 3MM.2 | R0204/2 | kdd-resistors | 1
R12 | 1K | 3MM.2 | R0204/2 | kdd-resistors | 1
R13 | 1.5K | 3MM.2 | R0204/2 | kdd-resistors | 1
R14 | 15K | 3MM.2 | R0204/2 | kdd-resistors | 1
R15 | 47K | 3MM.2 | R0204/2 | kdd-resistors | 1
R16 | 22K | 3MM.2 | R0204/2 | kdd-resistors | 1
R17 | 27K | 3MM.2 | R0204/2 | kdd-resistors | 1
R18 | 22K | 3MM.2 | R0204/2 | kdd-resistors | 1
R19 | 392K | 3MM.2 | R0204/2 | kdd-resistors | 1
R20 | 1.8K | 3MM.2 | R0204/2 | kdd-resistors | 1
R21 | 100K | 3MM.2 | R0204/2 | kdd-resistors | 1
R22 | 100K | 3MM.2 | R0204/2 | kdd-resistors | 1
R23 | 4.7K | 3MM.2 | R0204/2 | kdd-resistors | 1
R24 | 560r | 3MM.2 | R0204/2 | kdd-resistors | 1
R25 | 27K | 3MM.2 | R0204/2 | kdd-resistors | 1
R26 | 27K | 3MM.2 | R0204/2 | kdd-resistors | 1

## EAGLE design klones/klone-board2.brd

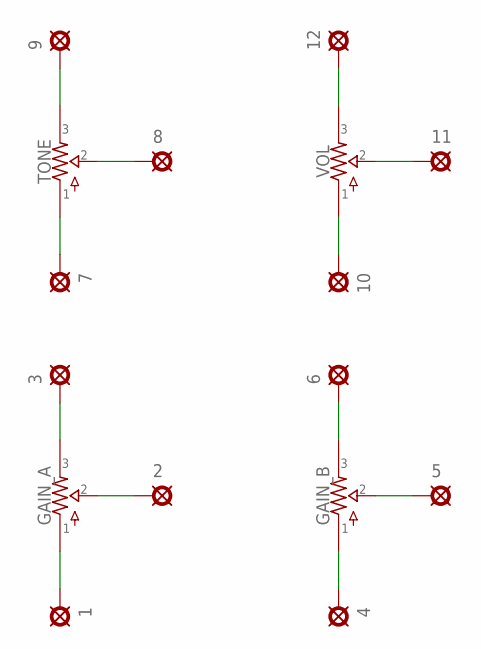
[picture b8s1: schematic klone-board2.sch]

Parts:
1, 2, 3, 4, 5, 6, 7, 8, 9, 10, 11, 12: PAD; SQUARE
GAIN: DUALGANG; 9MM_DUALGANG
TONE: POTS9MM_MOUNTED_2MMH; 9MM_W/MOUNTS-2MMHOLES
VOL: POTS9MM_MOUNTED_2MMH; 9MM_W/MOUNTS-2MMHOLES

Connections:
unnamed: 9.1, TONE.P$3 (3)
unnamed: 8.1, TONE.P$2 (2)
unnamed: 7.1, TONE.P$1 (1)
unnamed: 3.1, GAIN.3
unnamed: 2.1, GAIN.2
unnamed: 1.1, GAIN.1
unnamed: 4.1, GAIN.4 (1)
unnamed: 5.1, GAIN.5 (2)
unnamed: 6.1, GAIN.6 (3)
unnamed: 10.1, VOL.P$1 (1)
unnamed: 11.1, VOL.P$2 (2)
unnamed: 12.1, VOL.P$3 (3)

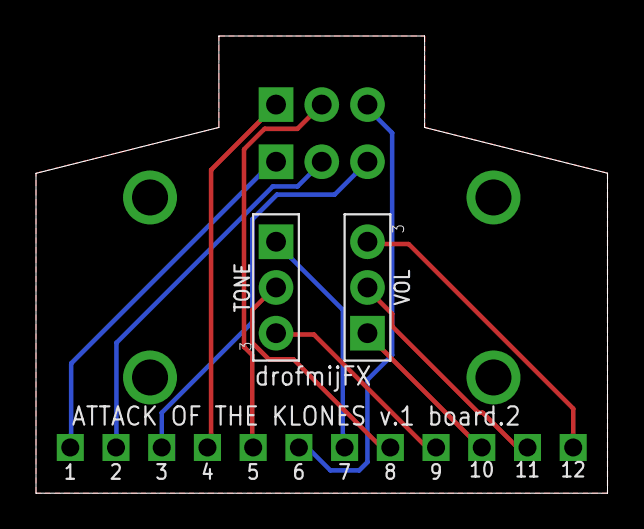
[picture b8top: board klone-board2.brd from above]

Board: 2 copper layers, 31.8 x 25.4 mm, 15 parts (1 on the bottom side), 12 nets.

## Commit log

2017-09-26 initial commit of Attack of the Klones 2 board version with BOM
2017-09-26 added link to attack of the klones
2017-09-26 more markdown changes
2018-09-06 Added Bajaman's AD200B project
2018-09-06 added link to mandarin
2019-02-25 added Chugga Choo Choo V1
2019-02-26 ChooChoo 2 Board pup style V1
2019-02-26 deleted some extra files
2026-02-24 added duende not sure if this version works
2026-02-24 zipped duended snapshot
